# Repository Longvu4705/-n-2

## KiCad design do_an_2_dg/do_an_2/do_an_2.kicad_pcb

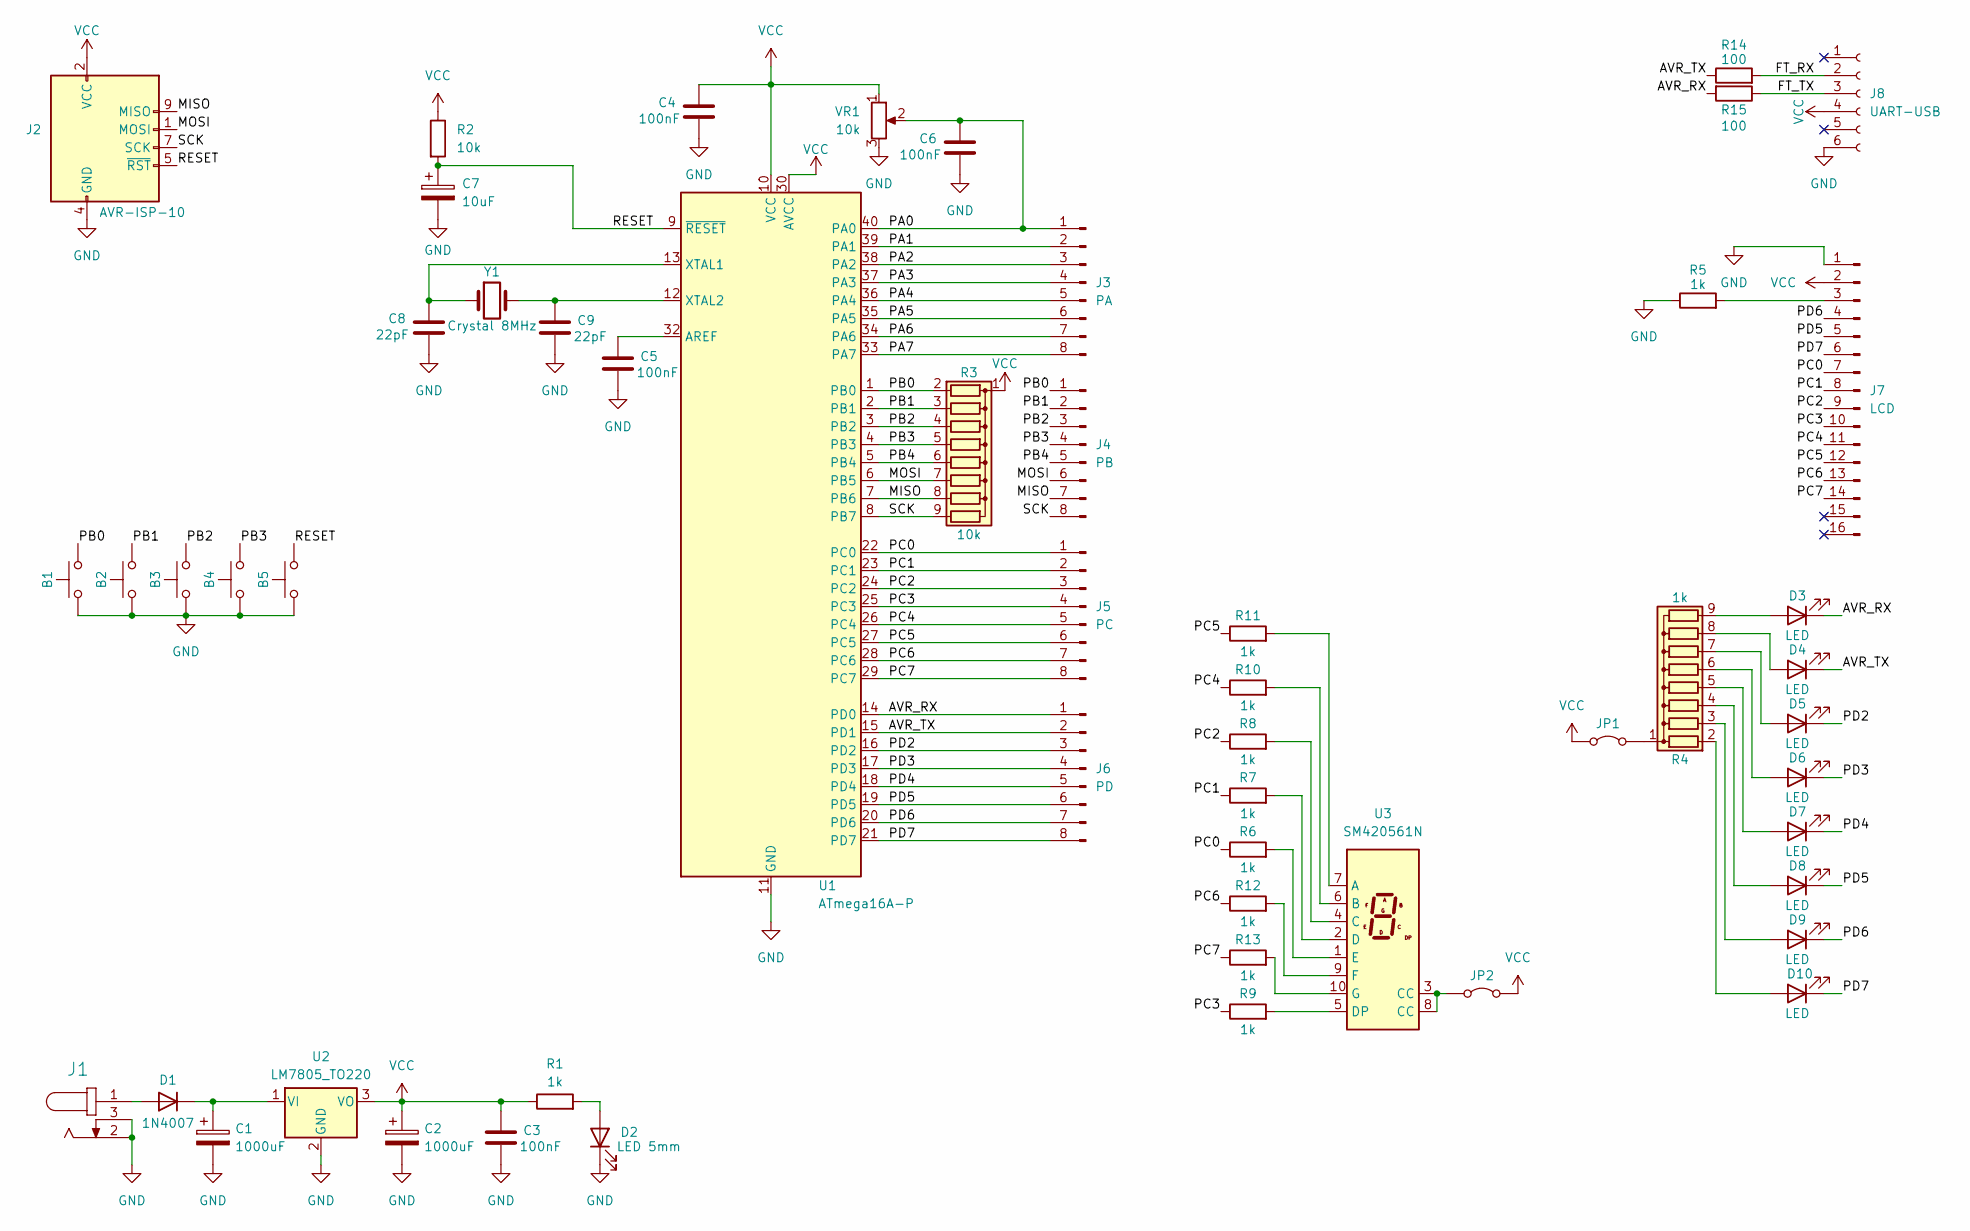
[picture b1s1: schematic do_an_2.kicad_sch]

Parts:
B1, B2, B3, B4, B5: SW_Push
C1, C2: 1000uF
C3, C4, C5, C6: 100nF
C7: 10uF
C8, C9: 22pF
D1: 1N4007; D_DO-41_SOD81_P10.16mm_Horizontal
D2: LED 5mm
D3, D4, D5, D6, D7, D8, D9, D10: LED
J1: *; CUI_PJ-202A
J2: AVR-ISP-10
J3: PA
J4: PB
J5: PC
J6: PD
J7: LCD
J8: UART-USB
JP1, JP2: Jumper_2_Bridged
R1, R5, R6, R7, R8, R9, R10, R11, R12, R13: 1k
R2: 10k
R3: 10k; R_Array_SIP9
R4: 1k; R_Array_SIP9
R14, R15: 100
U1: ATmega16A-P; DIP-40_W15.24mm
U2: LM7805_TO220; TO-220-3_Vertical
U3: SM420561N; 7SegmentLED_LTS6760_LTS6780
VR1: 10k
Y1: Crystal 8MHz

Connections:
/AVR_RX: D3.1 (K), J6.1, R15.2, U1.14 (PD0)
/AVR_TX: D4.1 (K), J6.2, R14.1, U1.15 (PD1)
/FT_RX: J8.2, R14.2
/FT_TX: J8.3, R15.1
/MISO: J2.9 (MISO), J4.7, R3.8 (R7), U1.7 (PB6)
/MOSI: J2.1 (MOSI), J4.6, R3.7 (R6), U1.6 (PB5)
/PA0: C6.1, J3.1, U1.40 (PA0), VR1.2
/PA1: J3.2, U1.39 (PA1)
/PA2: J3.3, U1.38 (PA2)
/PA3: J3.4, U1.37 (PA3)
/PA4: J3.5, U1.36 (PA4)
/PA5: J3.6, U1.35 (PA5)
/PA6: J3.7, U1.34 (PA6)
/PA7: J3.8, U1.33 (PA7)
/PB0: B1.2, J4.1, R3.2 (R1), U1.1 (PB0)
/PB1: B2.2, J4.2, R3.3 (R2), U1.2 (PB1)
/PB2: B3.2, J4.3, R3.4 (R3), U1.3 (PB2)
/PB3: B4.2, J4.4, R3.5 (R4), U1.4 (PB3)
/PB4: J4.5, R3.6 (R5), U1.5 (PB4)
/PC0: J5.1, J7.7, R6.1, U1.22 (PC0)
/PC1: J5.2, J7.8, R7.1, U1.23 (PC1)
/PC2: J5.3, J7.9, R8.1, U1.24 (PC2)
/PC3: J5.4, J7.10, R9.1, U1.25 (PC3)
/PC4: J5.5, J7.11, R10.1, U1.26 (PC4)
/PC5: J5.6, J7.12, R11.1, U1.27 (PC5)
/PC6: J5.7, J7.13, R12.1, U1.28 (PC6)
/PC7: J5.8, J7.14, R13.1, U1.29 (PC7)
/PD2: D5.1 (K), J6.3, U1.16 (PD2)
/PD3: D6.1 (K), J6.4, U1.17 (PD3)
/PD4: D7.1 (K), J6.5, U1.18 (PD4)
/PD5: D8.1 (K), J6.6, J7.5, U1.19 (PD5)
/PD6: D9.1 (K), J6.7, J7.4, U1.20 (PD6)
/PD7: D10.1 (K), J6.8, J7.6, U1.21 (PD7)
/RESET: B5.2, C7.1, J2.5 (~RST), R2.2, U1.9 (~RESET)
/SCK: J2.7 (SCK), J4.8, R3.9 (R8), U1.8 (PB7)
GND: B1.1, B2.1, B3.1, B4.1, B5.1, C1.2, C2.2, C3.2, C4.2, C5.2, C6.2, C7.2, C8.2, C9.2, D2.1 (K), J1.2, J1.3, J2.4 (GND), J2.6 (GND), J2.8 (GND), J2.10 (GND), J7.1, J8.6, R5.1, U1.11 (GND), U1.31 (GND), U2.2 (GND), VR1.3
unnamed: D1.2 (A), J1.1
unnamed: C1.1, D1.1 (K), U2.1 (VI)
unnamed: D2.2 (A), R1.2
unnamed: D3.2 (A), R4.9 (R8)
unnamed: D4.2 (A), R4.8 (R7)
unnamed: D5.2 (A), R4.7 (R6)
unnamed: D6.2 (A), R4.6 (R5)
unnamed: D7.2 (A), R4.5 (R4)
unnamed: D8.2 (A), R4.4 (R3)
unnamed: D9.2 (A), R4.3 (R2)
unnamed: D10.2 (A), R4.2 (R1)
unnamed: J7.3, R5.2
unnamed: JP1.2 (B), R4.1 (common)
unnamed: JP2.2 (B), U3.3 (CC), U3.8 (CC)
unnamed: C5.1, U1.32 (AREF)
unnamed: C8.1, U1.13 (XTAL1), Y1.1
unnamed: C9.1, U1.12 (XTAL2), Y1.2
unnamed: R11.2, U3.7 (A)
unnamed: R10.2, U3.6 (B)
unnamed: R8.2, U3.4 (C)
unnamed: R7.2, U3.2 (D)
unnamed: R9.2, U3.5 (DP)
unnamed: R6.2, U3.1 (E)
unnamed: R12.2, U3.9 (F)
unnamed: R13.2, U3.10 (G)
VCC: C2.1, C3.1, C4.1, J2.2 (VCC), J7.2, J8.4, JP1.1 (A), JP2.1 (A), R1.1, R2.1, R3.1 (common), U1.10 (VCC), U1.30 (AVCC), U2.3 (VO), VR1.1

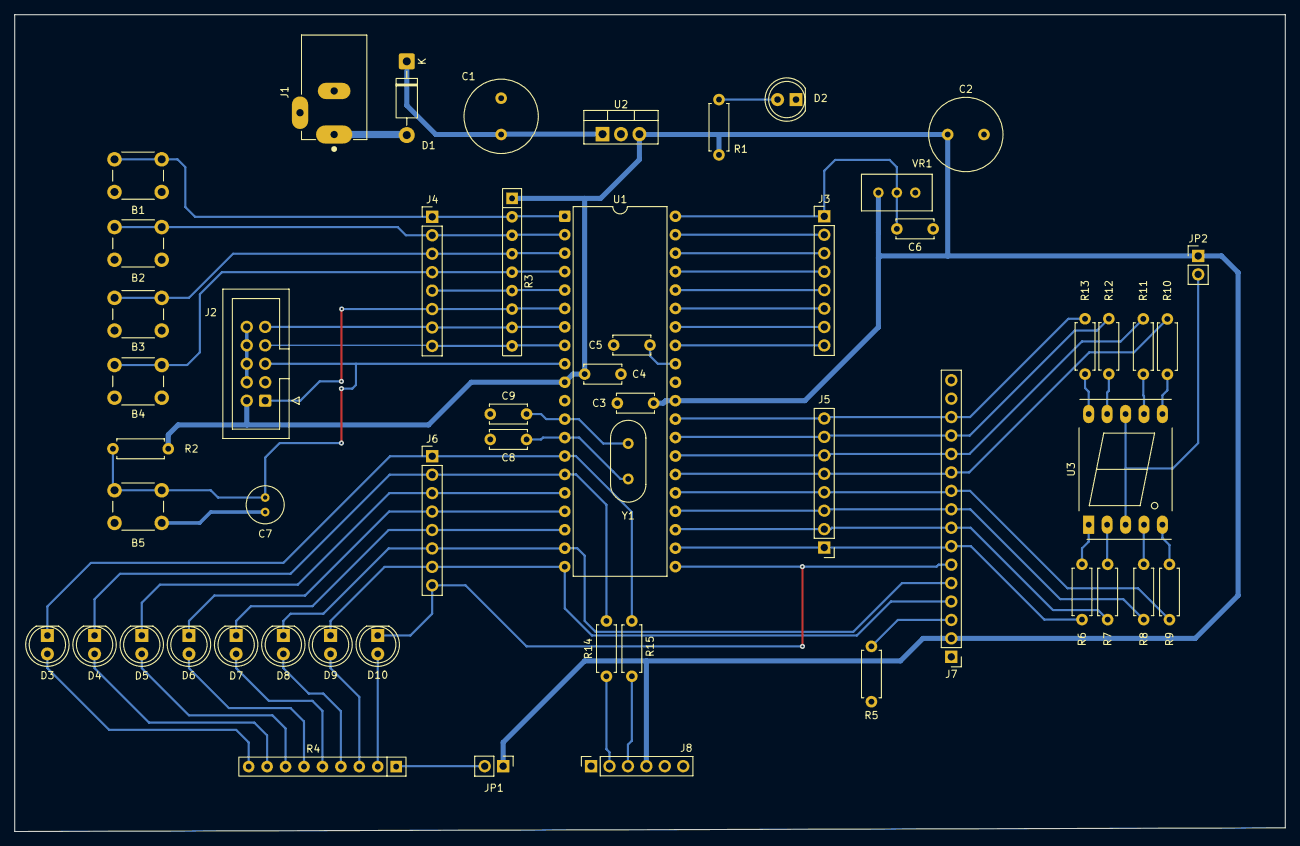
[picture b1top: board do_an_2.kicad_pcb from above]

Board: 2 copper layers, 175.0 x 112.5 mm, 54 parts (0 on the bottom side), 62 nets.

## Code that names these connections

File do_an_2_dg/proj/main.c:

#include <mega16.h>
#include <delay.h>
#include <stdio.h>

/* =========================
   CAU HINH LCD THEO MACH
   RS -> PD6
   RW -> PD5
   E  -> PD7
   D4 -> PC4
   D5 -> PC5
   D6 -> PC6
   D7 -> PC7
   ========================= */
#define LCD_RS PORTD.6
#define LCD_RW PORTD.5
#define LCD_E  PORTD.7

#define LCD_RS_DDR DDRD.6
#define LCD_RW_DDR DDRD.5
#define LCD_E_DDR  DDRD.7

/* =========================
   CAU HINH DS18B20
   DQ -> PA7
   Co dien tro keo len 4.7k
   ========================= */

#define OW_DQ_PORT PORTA.7
#define OW_DQ_DDR  DDRA.7
#define OW_DQ_PIN  PINA.7

/* =========================
   HAM LCD 4 BIT
   ========================= */

void lcd_enable(void)
{
    LCD_E = 1;
    delay_us(2);
    LCD_E = 0;
    delay_us(100);
}

void lcd_send_nibble(unsigned char data)
{
    PORTC = (PORTC & 0x0F) | ((data & 0x0F) << 4);
    lcd_enable();
}

void lcd_send_byte(unsigned char data, unsigned char rs)
{
    LCD_RW = 0;      // LCD luon o che do ghi
    LCD_RS = rs;

    // Gui 4 bit cao
    lcd_send_nibble(data >> 4);

    // Gui 4 bit thap
    lcd_send_nibble(data & 0x0F);
}

void lcd_cmd(unsigned char cmd)
{
    lcd_send_byte(cmd, 0);

    if (cmd == 0x01 || cmd == 0x02)
        delay_ms(2);
    else
        delay_us(100);
}

void lcd_data(unsigned char data)
{
    lcd_send_byte(data, 1);
}

void lcd_init_custom(void)
{
    // PC4-PC7 la output
    DDRC |= 0xF0;

    // PD5, PD6, PD7 la output
    LCD_RS_DDR = 1;
    LCD_RW_DDR = 1;
    LCD_E_DDR  = 1;

    LCD_RS = 0;
    LCD_RW = 0;
    LCD_E  = 0;

    delay_ms(20);

    // Khoi tao LCD 4-bit
    lcd_send_nibble(0x03);
    delay_ms(5);

    lcd_send_nibble(0x03);
    delay_us(150);

    lcd_send_nibble(0x03);
    delay_us(150);

    lcd_send_nibble(0x02);   // chuyen sang che do 4-bit

    lcd_cmd(0x28);           // 4-bit, 2 dong, font 5x8
    lcd_cmd(0x0C);           // bat hien thi, tat con tro
    lcd_cmd(0x06);           // tu dong tang vi tri con tro
    lcd_cmd(0x01);           // xoa man hinh
}

void lcd_gotoxy(unsigned char x, unsigned char y)
{
    if (y == 0)
        lcd_cmd(0x80 + x);
    else
        lcd_cmd(0xC0 + x);
}

void lcd_puts_custom(char *s)
{
    while (*s)
    {
        lcd_data(*s);
        s++;
    }
}

/* =========================
   HAM 1-WIRE CHO DS18B20
   ========================= */

void ow_low(void)
{
    OW_DQ_PORT = 0;
    OW_DQ_DDR = 1;      // PA7 output, keo bus xuong 0
}

void ow_release(void)
{
    OW_DQ_DDR = 0;      // PA7 input, nha bus
    OW_DQ_PORT = 1;     // Bat pull-up noi bo
}

unsigned char ow_read_pin(void)
{
    return OW_DQ_PIN;
}

unsigned char ow_reset(void)
{
    unsigned char presence;

    ow_low();
    delay_us(500);

    ow_release();
    delay_us(70);

    presence = !ow_read_pin();

    delay_us(410);

    return presence;
}

void ow_write_bit(unsigned char bit_value)
{
    if (bit_value)
    {
        ow_low();
        delay_us(6);
        ow_release();
        delay_us(64);
    }
    else
    {
        ow_low();
        delay_us(60);
        ow_release();
        delay_us(10);
    }
}

unsigned char ow_read_bit(void)
{
    unsigned char bit_value;

    ow_low();
    delay_us(6);

    ow_release();
    delay_us(9);

    bit_value = ow_read_pin();

    delay_us(55);

    return bit_value;
}

void ow_write_byte(unsigned char data)
{
    unsigned char i;

    for (i = 0; i < 8; i++)
    {
        ow_write_bit(data & 0x01);
        data >>= 1;
    }
}

unsigned char ow_read_byte(void)
{
    unsigned char i;
    unsigned char data = 0;

    for (i = 0; i < 8; i++)
    {
        if (ow_read_bit())
            data |= (1 << i);
    }

    return data;
}

/* =========================
   DOC NHIET DO DS18B20
   Tra ve nhiet do x10
   Vi du: 27.0 do C -> 270
   ========================= */

signed int ds18b20_read_temp_x10(void)
{
    unsigned char temp_lsb;
    unsigned char temp_msb;
    signed int raw;
    signed long temp_x10;

    if (!ow_reset())
    {
        return 9999;    // loi khong thay cam bien
    }

    ow_write_byte(0xCC);    // Skip ROM
    ow_write_byte(0x44);    // Convert T

    delay_ms(750);          // cho DS18B20 do xong

    if (!ow_reset())
    {
        return 9999;
    }

    ow_write_byte(0xCC);    // Skip ROM
    ow_write_byte(0xBE);    // Read Scratchpad

    temp_lsb = ow_read_byte();
    temp_msb = ow_read_byte();

    raw = ((signed int)temp_msb << 8) | temp_lsb;

    // DS18B20 mac dinh 12-bit: nhiet do = raw / 16
    // temp_x10 = nhiet do * 10 = raw * 10 / 16
    temp_x10 = ((signed long)raw * 10) / 16;

    return (signed int)temp_x10;
}

void lcd_show_temperature(signed int temp_x10)
{
    char buffer[10];
    signed int temp_abs;

    lcd_gotoxy(0, 0);
    lcd_puts_custom("Nhiet do:       ");

    lcd_gotoxy(4, 1);

    if (temp_x10 == 9999)
    {
        lcd_puts_custom("Sensor Error");
        return;
    }

    if (temp_x10 < 0)
    {
        lcd_data('-');
        temp_abs = -temp_x10;
    }
    else
    {
        temp_abs = temp_x10;
    }

    sprintf(buffer, "%d.%d", temp_abs / 10, temp_abs % 10);

    lcd_puts_custom(buffer);
    lcd_data(0xDF);      // ky tu do tren LCD1602
    lcd_data('C');
    lcd_puts_custom("     ");
}

/* =========================
   CHUONG TRINH CHINH
   ========================= */

void main(void)
{
    signed int temperature;

    // Tat JTAG vi LCD dung PC4, PC5
    // Neu khong tat, PC4/PC5 co the khong dieu khien LCD dung
    MCUCSR |= 0x80;
    MCUCSR |= 0x80;
    
    DDRA = 0x00;
    PORTA = 0x00;

    OW_DQ_DDR = 0;
    OW_DQ_PORT = 1;

    lcd_init_custom();

    lcd_gotoxy(0, 0);
    lcd_puts_custom("ATmega16");
    lcd_gotoxy(0, 1);
    lcd_puts_custom("DS18B20 Ready");
    delay_ms(1000);

    lcd_cmd(0x01);

    while (1)
    {
        temperature = ds18b20_read_temp_x10();

        lcd_show_temperature(temperature);

        delay_ms(500);
    }
}
